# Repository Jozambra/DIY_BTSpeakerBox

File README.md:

# DIY_BTSpeakerBox
This project presents a DIY design for a speaker box that can recieve audio data from an analog 3.5mm Jack or a BT module. It incorporates a 3-band Equalizer custom PCB that also functions as the main power distribution board.

Rev history:

1.0 - Original Issue

1.1 - Holes for potentiometers and 3.5mm jack were enlarged based on the testing executed with the files of Rev 1.0

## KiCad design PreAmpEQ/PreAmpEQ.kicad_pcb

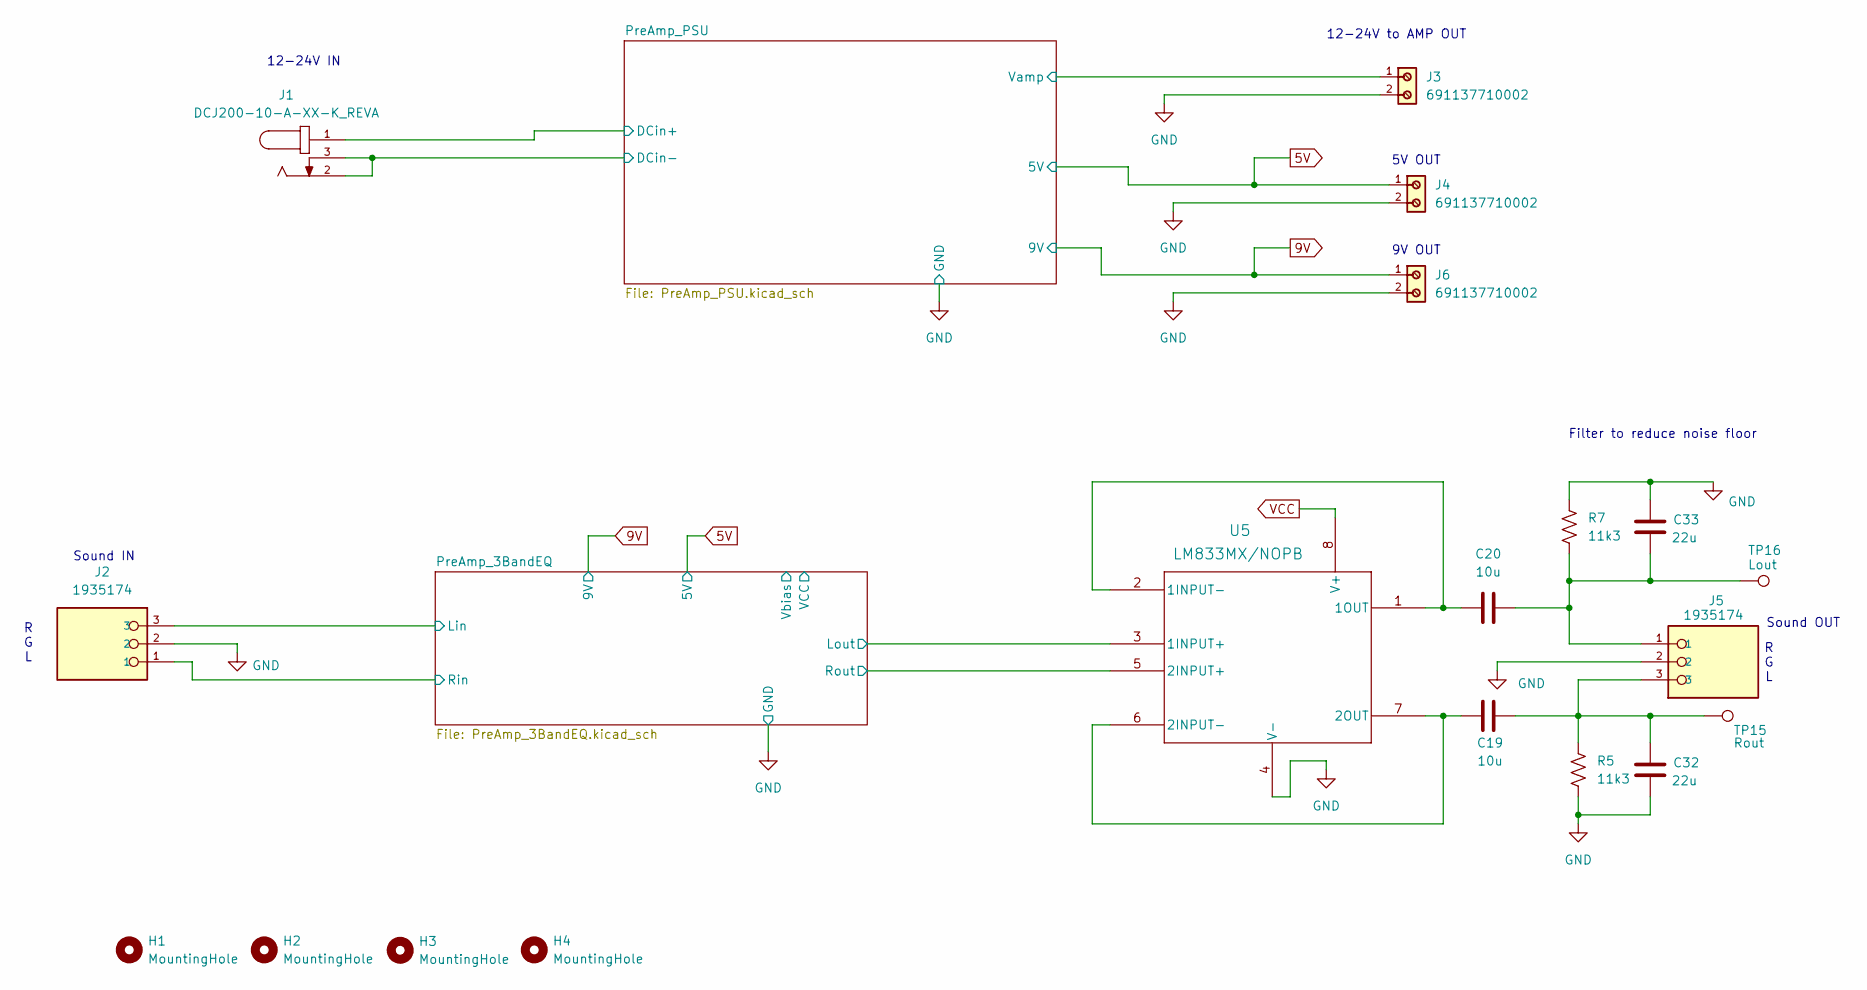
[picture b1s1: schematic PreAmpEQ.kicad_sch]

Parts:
C19, C20: 10u; C_0805_2012Metric_Pad1.18x1.45mm_HandSolder
C32, C33: 22u; C_0805_2012Metric_Pad1.18x1.45mm_HandSolder
H1, H2, H3, H4: MountingHole; MountingHole_3.2mm_M3
J1: DCJ200-10-A-XX-K_REVA; GCT_DCJ200-10-A-XX-K_REVA; PARTREV A
J2, J5: 1935174; PHOENIX_1935174
J3, J4, J6: 691137710002; PART-NUMBER 691137710002
R5, R7: 11k3; R_0805_2012Metric_Pad1.20x1.40mm_HandSolder
TP15: Rout; TestPoint_Loop_D2.50mm_Drill1.85mm
TP16: Lout; TestPoint_Loop_D2.50mm_Drill1.85mm
U5: LM833MX/NOPB; M08A_TEX

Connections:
5V: J4.1; also elsewhere on the board
9V: J6.1; also elsewhere on the board
/PreAmp_3BandEQ/Lin: J2.3; also elsewhere on the board
/PreAmp_3BandEQ/Lout: U5.3 (1INPUT+); also elsewhere on the board
/PreAmp_3BandEQ/Rin: J2.1; also elsewhere on the board
/PreAmp_3BandEQ/Rout: U5.5 (2INPUT+); also elsewhere on the board
/PreAmp_PSU/DCin+: J1.1; also elsewhere on the board
/PreAmp_PSU/DCin-: J1.2, J1.3; also elsewhere on the board
/PreAmp_PSU/Vamp: J3.1; also elsewhere on the board
GND: C32.2, C33.1, J2.2, J3.2, J4.2, J5.2, J6.2, R5.2, R7.2, U5.4 (V-); also elsewhere on the board
unnamed: C19.1, C32.1, J5.3, R5.1, TP15.1
unnamed: C20.2, C33.2, J5.1, R7.1, TP16.1
unnamed: C20.1, U5.1 (1OUT), U5.2 (1INPUT-)
unnamed: C19.2, U5.6 (2INPUT-), U5.7 (2OUT)
VCC: U5.8 (V+); also elsewhere on the board

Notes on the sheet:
5V OUT
9V OUT
12-24V IN
Sound OUT
Filter to reduce noise floor
Sound IN
12-24V to AMP OUT
R G L

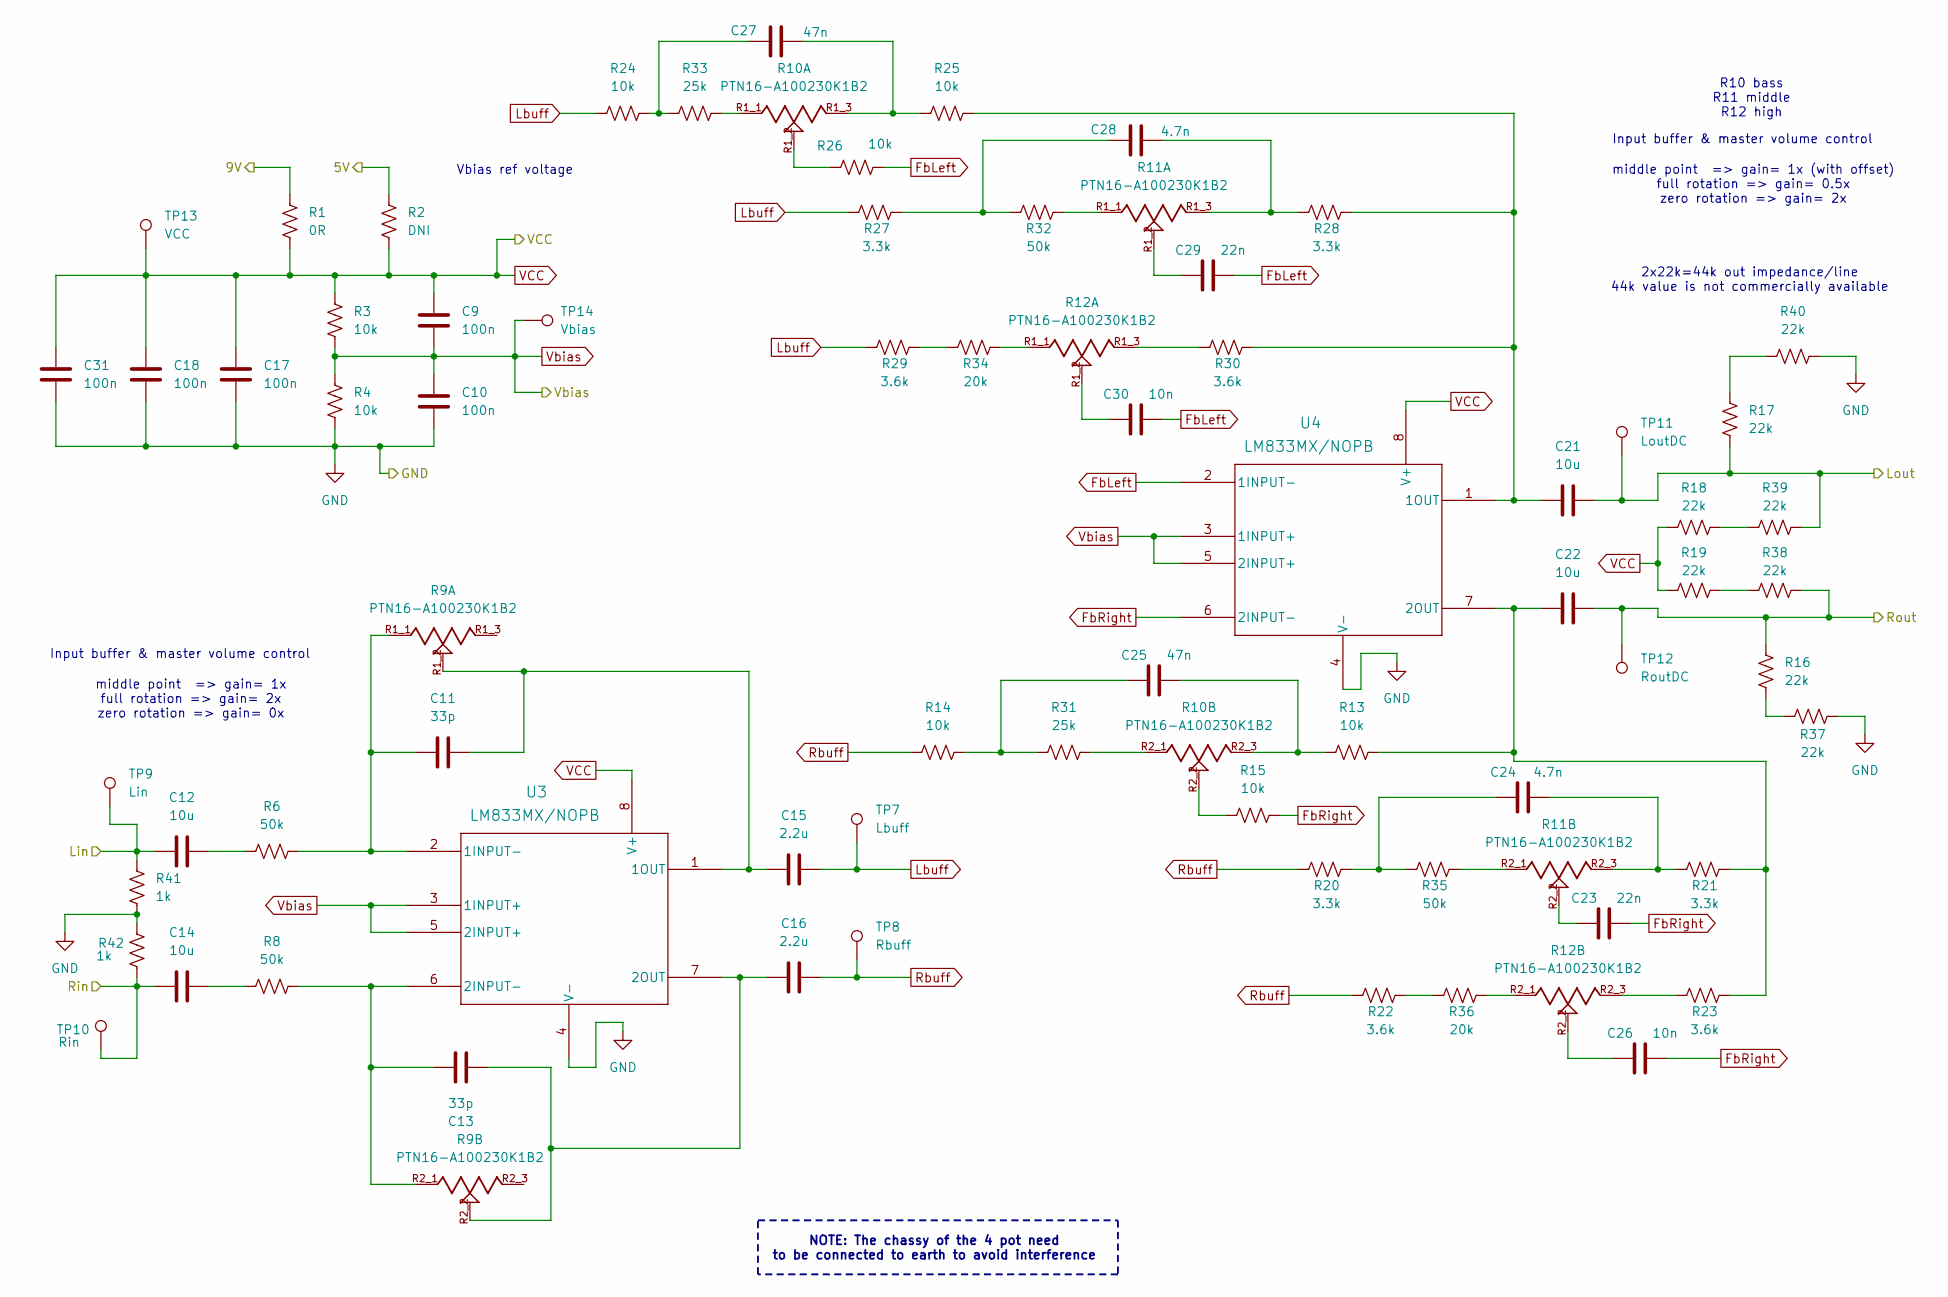
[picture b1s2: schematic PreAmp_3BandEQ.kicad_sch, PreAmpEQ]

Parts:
C9, C10, C17, C18, C31: 100n; C_0805_2012Metric_Pad1.18x1.45mm_HandSolder
C11, C13: 33p; C_0805_2012Metric_Pad1.18x1.45mm_HandSolder
C12, C14, C21, C22: 10u; C_0805_2012Metric_Pad1.18x1.45mm_HandSolder
C15, C16: 2.2u; C_0805_2012Metric_Pad1.18x1.45mm_HandSolder
C23, C29: 22n; C_0805_2012Metric_Pad1.18x1.45mm_HandSolder
C24, C28: 4.7n; C_0805_2012Metric_Pad1.18x1.45mm_HandSolder
C25, C27: 47n; C_0805_2012Metric_Pad1.18x1.45mm_HandSolder
C26, C30: 10n; C_0805_2012Metric_Pad1.18x1.45mm_HandSolder
R1: 0R; R_0805_2012Metric_Pad1.20x1.40mm_HandSolder
R2: DNI; R_0805_2012Metric_Pad1.20x1.40mm_HandSolder
R3, R4, R13, R14, R15, R24, R25, R26: 10k; R_0805_2012Metric_Pad1.20x1.40mm_HandSolder
R6, R8, R32, R35: 50k; R_0805_2012Metric_Pad1.20x1.40mm_HandSolder
R9, R10, R11, R12: PTN16-A100230K1B2; POT_PTN16-A100230K1B2; PARTREV 1.0
R16, R17, R18, R19, R37, R38, R39, R40: 22k; R_0805_2012Metric_Pad1.20x1.40mm_HandSolder
R20, R21, R27, R28: 3.3k; R_0805_2012Metric_Pad1.20x1.40mm_HandSolder
R22, R23, R29, R30: 3.6k; R_0805_2012Metric_Pad1.20x1.40mm_HandSolder
R31, R33: 25k; R_0805_2012Metric_Pad1.20x1.40mm_HandSolder
R34, R36: 20k; R_0805_2012Metric_Pad1.20x1.40mm_HandSolder
R41, R42: 1k; R_0805_2012Metric_Pad1.20x1.40mm_HandSolder
TP7: Lbuff; TestPoint_Loop_D2.50mm_Drill1.85mm
TP8: Rbuff; TestPoint_Loop_D2.50mm_Drill1.85mm
TP9: Lin; TestPoint_Loop_D2.50mm_Drill1.85mm
TP10: Rin; TestPoint_Loop_D2.50mm_Drill1.85mm
TP11: LoutDC; TestPoint_Loop_D2.50mm_Drill1.85mm
TP12: RoutDC; TestPoint_Loop_D2.50mm_Drill1.85mm
TP13: VCC
TP14: Vbias
U3, U4: LM833MX/NOPB; M08A_TEX

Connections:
5V: R2.1; also elsewhere on the board
9V: R1.1; also elsewhere on the board
/PreAmp_3BandEQ/Lin: C12.1, R41.2, TP9.1; also elsewhere on the board
/PreAmp_3BandEQ/Lout: C21.2, R17.2, R39.2, TP11.1; also elsewhere on the board
/PreAmp_3BandEQ/Rin: C14.1, R42.1, TP10.1; also elsewhere on the board
/PreAmp_3BandEQ/Rout: C22.2, R16.2, R38.2, TP12.1; also elsewhere on the board
FbLeft: C29.2, C30.2, R26.2, U4.2 (1INPUT-)
FbRight: C23.2, C26.2, R15.2, U4.6 (2INPUT-)
GND: C10.2, C17.2, C18.2, C31.2, R4.2, R37.2, R40.2, R41.1, R42.2, U3.4 (V-), U4.4 (V-); also elsewhere on the board
Lbuff: C15.2, R24.1, R27.1, R29.1, TP7.1
unnamed: C12.2, R6.1
unnamed: C14.2, R8.1
unnamed: C23.1, R11.R2_2
unnamed: C24.1, R20.2, R35.1
unnamed: C24.2, R11.R2_3, R21.1
unnamed: C25.1, R14.2, R31.1
unnamed: C25.2, R10.R2_3, R13.1
unnamed: C26.1, R12.R2_2
unnamed: C27.1, R24.2, R33.1
unnamed: C27.2, R10.R1_3, R25.1
unnamed: C28.1, R27.2, R32.1
unnamed: C28.2, R11.R1_3, R28.1
unnamed: C29.1, R11.R1_2
unnamed: C30.1, R12.R1_2
unnamed: R10.R1_1, R33.2
unnamed: R10.R1_2, R26.1
unnamed: R10.R2_1, R31.2
unnamed: R10.R2_2, R15.1
unnamed: R11.R1_1, R32.2
unnamed: R11.R2_1, R35.2
unnamed: R12.R1_1, R34.2
unnamed: R12.R1_3, R30.1
unnamed: R12.R2_1, R36.2
unnamed: R12.R2_3, R23.1
unnamed: R16.1, R37.1
unnamed: R17.1, R40.1
unnamed: R18.2, R39.1
unnamed: R19.2, R38.1
unnamed: R22.2, R36.1
unnamed: R29.2, R34.1
unnamed: C11.1, R6.2, R9.R1_1, U3.2 (1INPUT-)
unnamed: C11.2, C15.1, R9.R1_2, U3.1 (1OUT)
unnamed: C13.2, R8.2, R9.R2_1, U3.6 (2INPUT-)
unnamed: C13.1, C16.1, R9.R2_2, U3.7 (2OUT)
unnamed: C21.1, R25.2, R28.2, R30.2, U4.1 (1OUT)
unnamed: C22.1, R13.2, R21.2, R23.2, U4.7 (2OUT)
Rbuff: C16.2, R14.1, R20.1, R22.1, TP8.1
VCC: C9.1, C17.1, C18.1, C31.1, R1.2, R2.2, R3.1, R18.1, R19.1, TP13.1, U3.8 (V+), U4.8 (V+); also elsewhere on the board
Vbias: C9.2, C10.1, R3.2, R4.1, TP14.1, U3.3 (1INPUT+), U3.5 (2INPUT+), U4.3 (1INPUT+), U4.5 (2INPUT+)

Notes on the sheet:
R10 bass R11 middle R12 high
NOTE: The chassy of the 4 pot need to be connected to earth to avoid interference
2x22k=44k out impedance/line 44k value is not commercially available
Vbias ref voltage
Input buffer & master volume control
middle point => gain= 1x (with offset) full rotation => gain= 0.5x zero rotation => gain= 2x
middle point => gain= 1x full rotation => gain= 2x zero rotation => gain= 0x

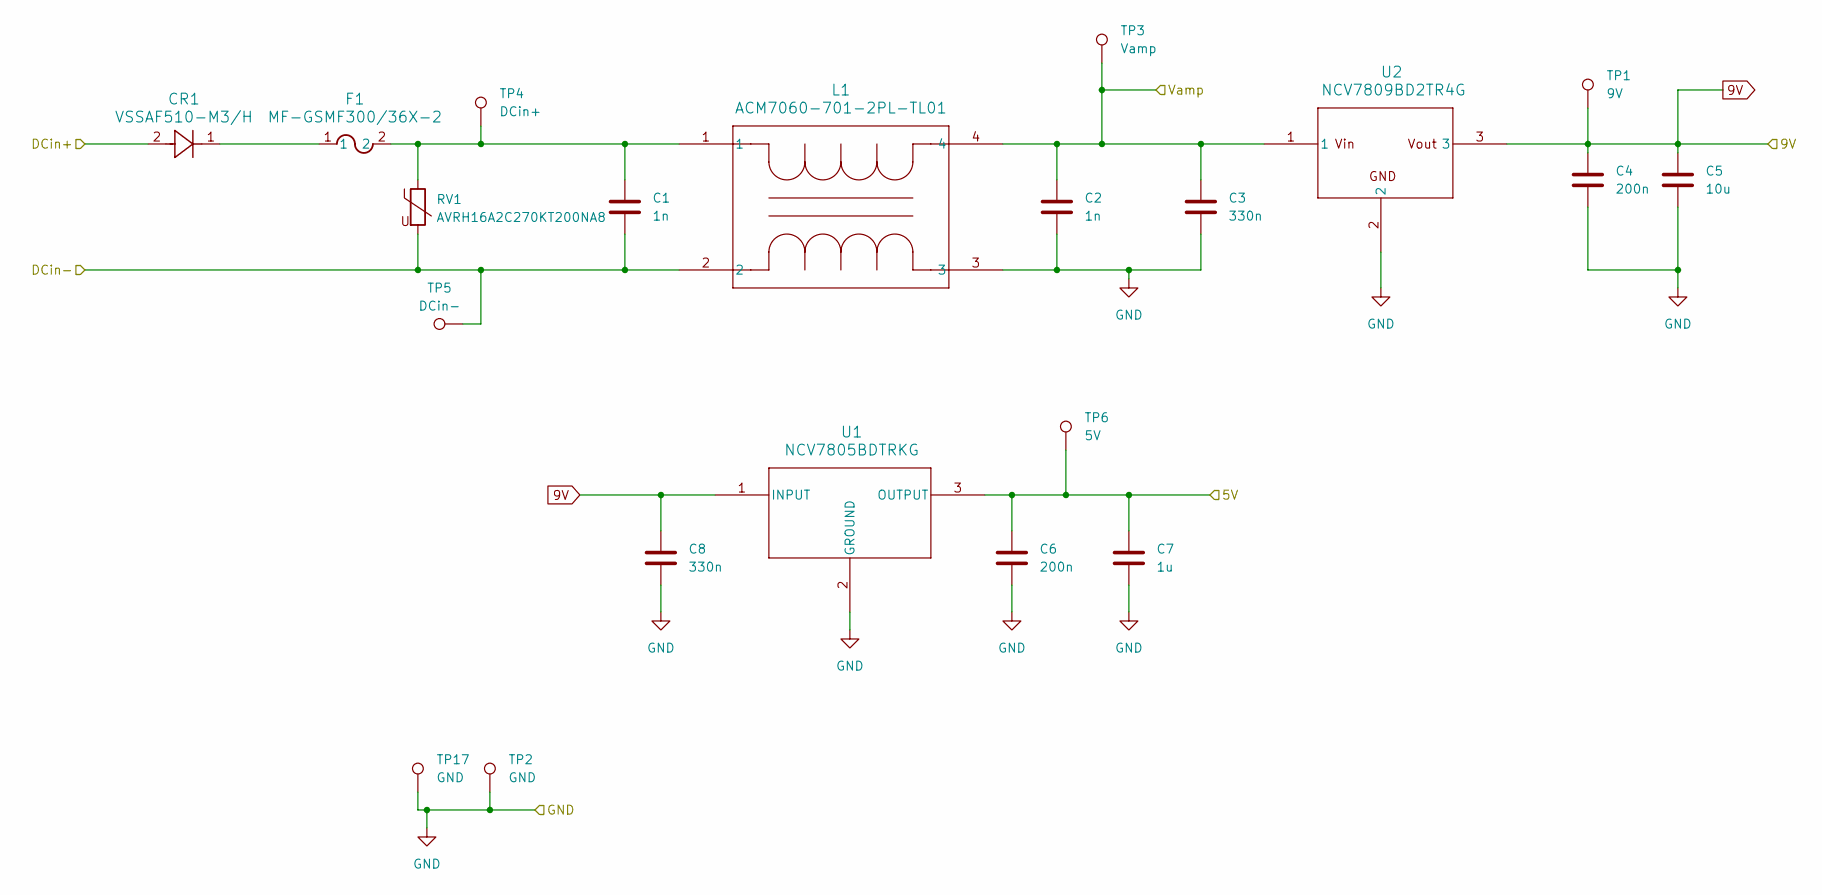
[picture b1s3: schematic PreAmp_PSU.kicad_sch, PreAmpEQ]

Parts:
C1, C2: 1n; C_0805_2012Metric_Pad1.18x1.45mm_HandSolder
C3, C8: 330n; C_0805_2012Metric_Pad1.18x1.45mm_HandSolder
C4, C6: 200n; C_0805_2012Metric_Pad1.18x1.45mm_HandSolder
C5: 10u; C_0805_2012Metric_Pad1.18x1.45mm_HandSolder
C7: 1u; C_0805_2012Metric_Pad1.18x1.45mm_HandSolder
CR1: VSSAF510-M3/H; CR_SLIMSMA_DO-221AC_VIS
F1: MF-GSMF300/36X-2; FUSE_MF-GSMF_BRN
L1: ACM7060-701-2PL-TL01; IND_ACM7060_TDK
RV1: AVRH16A2C270KT200NA8; R_0603_1608Metric_Pad0.98x0.95mm_HandSolder
TP1: 9V; TestPoint_Loop_D2.50mm_Drill1.85mm
TP2, TP17: GND; TestPoint_Loop_D2.50mm_Drill1.85mm
TP3: Vamp; TestPoint_Loop_D2.50mm_Drill1.85mm
TP4: DCin+; TestPoint_Loop_D2.50mm_Drill1.85mm
TP5: DCin-; TestPoint_Loop_D2.50mm_Drill1.85mm
TP6: 5V; TestPoint_Loop_D2.50mm_Drill1.85mm
U1: NCV7805BDTRKG; DPAK-3_ONS
U2: NCV7809BD2TR4G; D2PAK3_ONS

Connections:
5V: C6.1, C7.1, TP6.1, U1.3 (OUTPUT); also elsewhere on the board
9V: C4.1, C5.1, C8.1, TP1.1, U1.1 (INPUT), U2.3; also elsewhere on the board
/PreAmp_PSU/DCin+: CR1.2; also elsewhere on the board
/PreAmp_PSU/DCin-: C1.2, L1.2, RV1.2, TP5.1; also elsewhere on the board
/PreAmp_PSU/Vamp: C2.1, C3.1, L1.4, TP3.1, U2.1; also elsewhere on the board
GND: C2.2, C3.2, C4.2, C5.2, C6.2, C7.2, C8.2, L1.3, TP2.1, TP17.1, U1.2 (GROUND), U2.2, U2.4; also elsewhere on the board
unnamed: C1.1, F1.2, L1.1, RV1.1, TP4.1
unnamed: CR1.1, F1.1

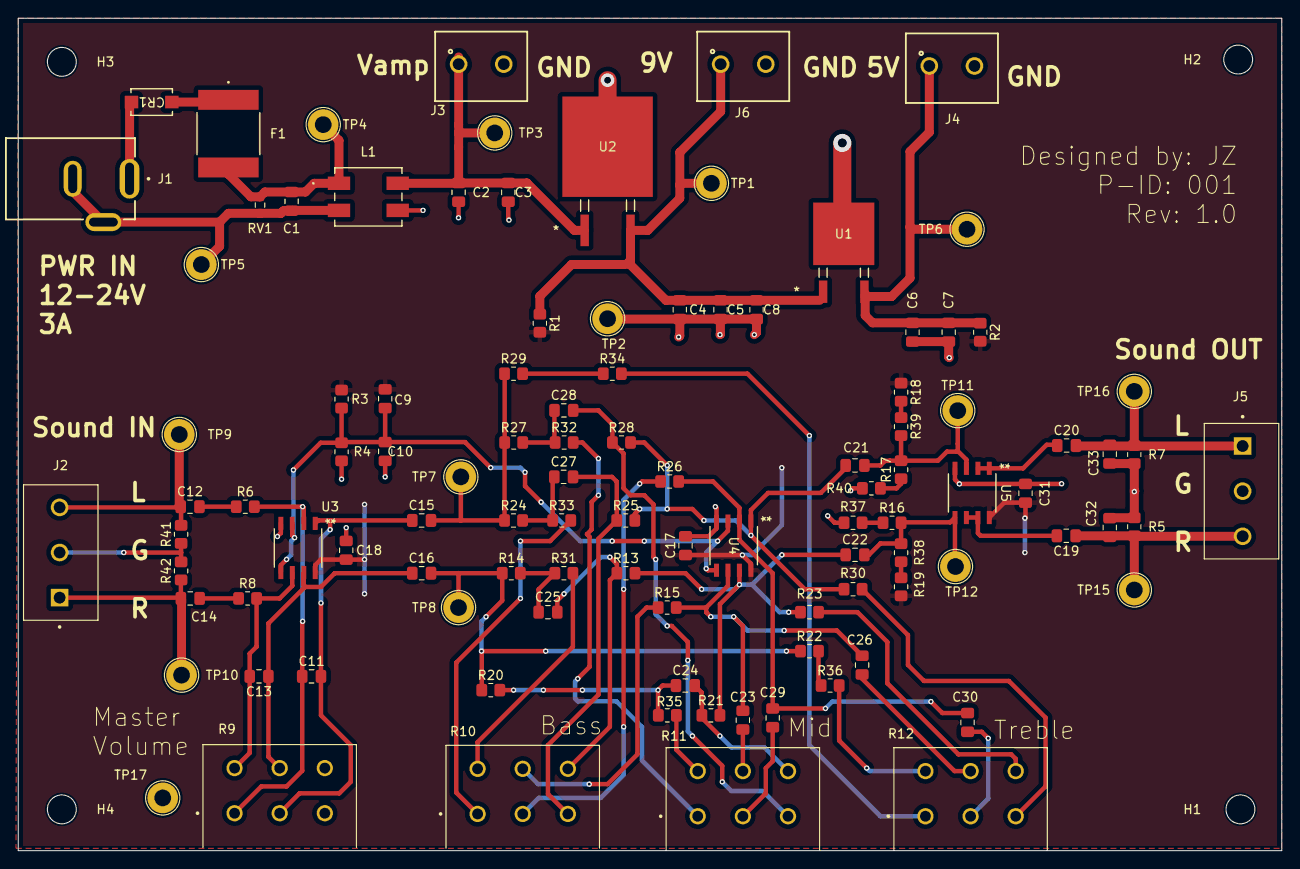
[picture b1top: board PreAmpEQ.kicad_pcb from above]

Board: 2 copper layers, 140.0 x 92.2 mm, 109 parts (0 on the bottom side), 58 nets.

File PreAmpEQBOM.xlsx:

Reference | Value | Qty | Datasheet | Footprint | DNP | added
C1,C2 | 1n | 2 | ~ | Capacitor_SMD:C_0805_2012Metric_Pad1.18x1.45mm_HandSolder
C3,C8 | 330n | 2 | ~ | Capacitor_SMD:C_0805_2012Metric_Pad1.18x1.45mm_HandSolder
C4,C6 | 200n | 2 | ~ | Capacitor_SMD:C_0805_2012Metric_Pad1.18x1.45mm_HandSolder
C5,C12,C14,C19,C20,C21,C22 | 10u | 7 | ~ | Capacitor_SMD:C_0805_2012Metric_Pad1.18x1.45mm_HandSolder
C7 | 1u | 1 | ~ | Capacitor_SMD:C_0805_2012Metric_Pad1.18x1.45mm_HandSolder
C9,C10,C17,C18,C31 | 100n | 5 | ~ | Capacitor_SMD:C_0805_2012Metric_Pad1.18x1.45mm_HandSolder
C11,C13 | 33p | 2 | ~ | Capacitor_SMD:C_0805_2012Metric_Pad1.18x1.45mm_HandSolder
C15,C16 | 2.2u | 2 | ~ | Capacitor_SMD:C_0805_2012Metric_Pad1.18x1.45mm_HandSolder
C23,C29 | 22n | 2 | ~ | Capacitor_SMD:C_0805_2012Metric_Pad1.18x1.45mm_HandSolder
C24,C28 | 4.7n | 2 | ~ | Capacitor_SMD:C_0805_2012Metric_Pad1.18x1.45mm_HandSolder
C25,C27 | 47n | 2 | ~ | Capacitor_SMD:C_0805_2012Metric_Pad1.18x1.45mm_HandSolder
C26,C30 | 10n | 2 | ~ | Capacitor_SMD:C_0805_2012Metric_Pad1.18x1.45mm_HandSolder
CR1 | VSSAF510-M3/H | 1 | VSSAF510-M3/H | CR_SLIMSMA_DO-221AC_VIS
F1 | MF-GSMF300/36X-2 | 1 | MF-GSMF300/36X-2 | MFGSM:FUSE_MF-GSMF_BRN
J1 | DCJ200-10-A-XX-K_REVA | 1 |  | DCJ200:GCT_DCJ200-10-A-XX-K_REVA
J2,J5 | 1935174 | 2 |  | TERM BLK 3POS:PHOENIX_1935174
J3,J4,J6 | 691137710002 | 3 |  | TERM BLK 2POS:691137710002
L1 | ACM7060-701-2PL-TL01 | 1 | ACM7060-701-2PL-TL01 | ACM7060:IND_ACM7060_TDK
R1 | 0R | 1 | ~ | Resistor_SMD:R_0805_2012Metric_Pad1.20x1.40mm_HandSolder
R2,R5,R7 | DNI | 3 | ~ | Resistor_SMD:R_0805_2012Metric_Pad1.20x1.40mm_HandSolder
R3,R4,R13,R14,R15,R24,R25,R26 | 10k | 8 | ~ | Resistor_SMD:R_0805_2012Metric_Pad1.20x1.40mm_HandSolder
R6,R8,R32,R35 | 50k | 4 | ~ | Resistor_SMD:R_0805_2012Metric_Pad1.20x1.40mm_HandSolder
R9,R10,R11,R12 | PTN16-A100230K1B2 | 4 |  | PTN16:POT_PTN16-A100230K1B2
R16,R17,R18,R19 | 44k | 4 | ~ | Resistor_SMD:R_0805_2012Metric_Pad1.20x1.40mm_HandSolder
R20,R21,R27,R28 | 3.3k | 4 | ~ | Resistor_SMD:R_0805_2012Metric_Pad1.20x1.40mm_HandSolder
R22,R23,R29,R30 | 3.6k | 4 | ~ | Resistor_SMD:R_0805_2012Metric_Pad1.20x1.40mm_HandSolder
R31,R33 | 25k | 2 | ~ | Resistor_SMD:R_0805_2012Metric_Pad1.20x1.40mm_HandSolder
R34,R36 | 20k | 2 | ~ | Resistor_SMD:R_0805_2012Metric_Pad1.20x1.40mm_HandSolder
RV1 | AVRH16A2C270KT200NA8 | 1 | ~ | Resistor_SMD:R_0603_1608Metric_Pad0.98x0.95mm_HandSolder
U1 | NCV7805BDTRKG | 1 | NCV7805BDTRKG | DPAK-3_ONS
U2 | NCV7809BD2TR4G | 1 | NCV7809BD2TR4G | D2PAK3_ONS
U3,U4,U5 | LM833MX/NOPB | 3 | LM833MX/NOPB | LM833MX:M08A_TEX

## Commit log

2025-03-09 Update README.md
    Detailed project description added
2025-03-09 Update README.md
    updated state of the main PCB mounting whole situation
2025-03-09 Update README.md
    added description about rev 1.1
2025-03-09 Added Electronic design files
    All the design files for the electronic/electrical section of the project is attached
2025-03-09 Added mechanical files
    The mechanical files of the project were added, this includes the FreeCAD master file and the 2 object file ready to be 3d printed
2025-03-09 Rev1.1 attached
    This revision enlarges the holes for the control potentionemeters and the 3.5mm audio jack
2025-03-09 Update README.md
    updated rev history with version 1.1
2025-03-09 Update README.md
    cosmetic changes to history presentation
